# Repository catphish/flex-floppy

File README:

NOTE: This project was never completed and will receive no further updates.

Please consider greaseweazle instead: https://github.com/keirf/greaseweazle

This repository remains only for reference.

========== FlexFloppy ===========
USB Multi-pupose Floppy Interface
=================================

This device allows floppy disks to be read and written using a low cost
USB interface and a generic floppy disk drive. It is targetted at
Amiga floppy disks but may support others. Currently only DD disks
are supported due to USB FS bandwidth constraints.

Data is read and written in raw flux format and will be stored in SCP
format for for maximum compatibility and flexibility.

This project is a work in progress.

Firmware TODO
=============
Timeout on missing index pulse during write

Host TODO
=========
Proper CLI toolkit
GUI

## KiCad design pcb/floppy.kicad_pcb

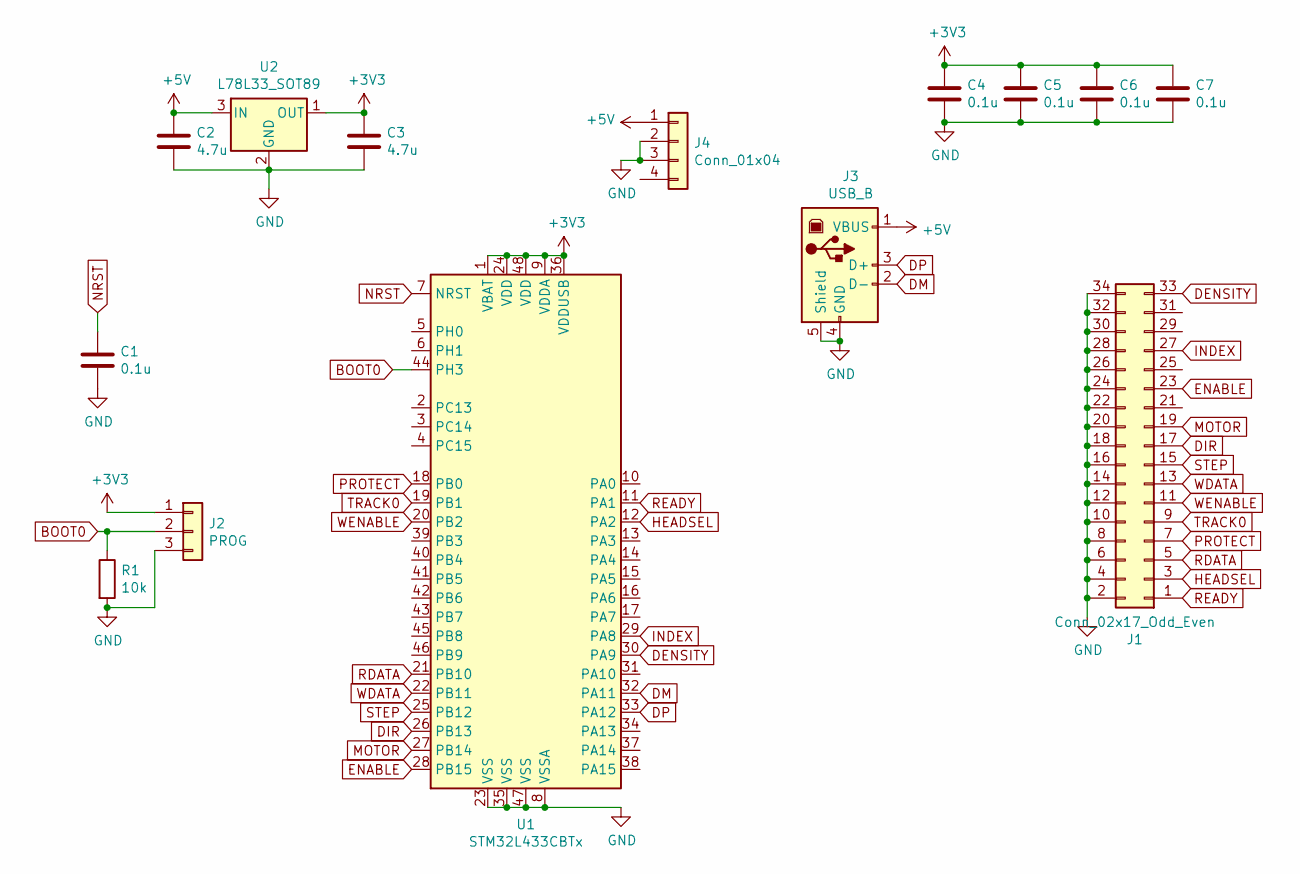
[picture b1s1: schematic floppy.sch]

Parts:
C1, C4, C5, C6, C7: 0.1u; C_0603_1608Metric
C2, C3: 4.7u; C_0603_1608Metric
J1: Conn_02x17_Odd_Even; PinSocket_2x17_P2.54mm_Horizontal
J2: PROG; PinHeader_1x03_P2.54mm_Vertical
J3: USB_B; USB_B_OST_USB-B1HSxx_Horizontal
J4: Conn_01x04; PinHeader_1x04_P2.54mm_Vertical
R1: 10k; R_0603_1608Metric
U1: STM32L433CBTx; LQFP-48_7x7mm_P0.5mm
U2: L78L33_SOT89; SOT-89-3

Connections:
+3V3: C3.1, C4.1, C5.1, C6.1, C7.1, J2.1, U1.1 (VBAT), U1.9 (VDDA), U1.24 (VDD), U1.36 (VDDUSB), U1.48 (VDD), U2.1 (OUT)
+5V: C2.1, J3.1 (VBUS), J4.1, U2.3 (IN)
BOOT0: J2.2, R1.1, U1.44 (PH3)
DENSITY: J1.33, U1.30 (PA9)
DIR: J1.17, U1.26 (PB13)
DM: J3.2 (D-), U1.32 (PA11)
DP: J3.3 (D+), U1.33 (PA12)
ENABLE: J1.23, U1.28 (PB15)
GND: C1.2, C2.2, C3.2, C4.2, C5.2, C6.2, C7.2, J1.2, J1.4, J1.6, J1.8, J1.10, J1.12, J1.14, J1.16, J1.18, J1.20, J1.22, J1.24, J1.26, J1.28, J1.30, J1.32, J1.34, J2.3, J3.4 (GND), J3.5 (Shield), J4.2, J4.3, R1.2, U1.8 (VSSA), U1.23 (VSS), U1.35 (VSS), U1.47 (VSS), U2.2 (GND)
HEADSEL: J1.3, U1.12 (PA2)
INDEX: J1.27, U1.29 (PA8)
MOTOR: J1.19, U1.27 (PB14)
NRST: C1.1, U1.7 (NRST)
PROTECT: J1.7, U1.18 (PB0)
RDATA: J1.5, U1.21 (PB10)
READY: J1.1, U1.11 (PA1)
STEP: J1.15, U1.25 (PB12)
TRACK0: J1.9, U1.19 (PB1)
WDATA: J1.13, U1.22 (PB11)
WENABLE: J1.11, U1.20 (PB2)

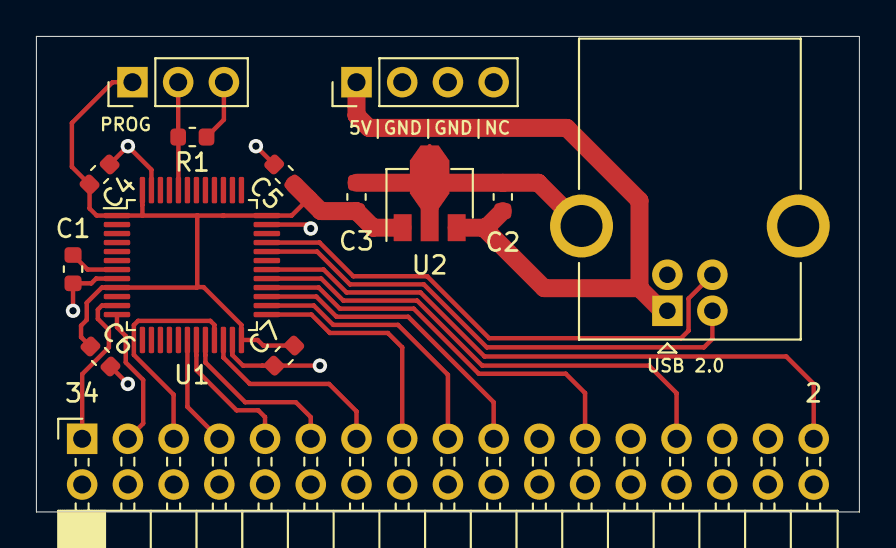
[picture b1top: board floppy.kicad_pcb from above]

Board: 2 copper layers, 45.7 x 26.4 mm, 14 parts (0 on the bottom side), 20 nets.

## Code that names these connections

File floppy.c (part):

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
  gpio_port_mode(GPIOA, 1, 0, 0, 1, 0);  // A1  READY     IN
  gpio_port_mode(GPIOA, 2, 1, 0, 0, 1);  // A2  HEADSELET OUT
  gpio_port_mode(GPIOA, 8, 0, 0, 1, 0);  // A8  INDEX     IN
  gpio_port_mode(GPIOA, 9, 1, 0, 0, 1);  // A9  DENSITY   OUT

  gpio_port_mode(GPIOB, 0, 0, 0, 1, 0);  // B0  PROTECT   IN
  gpio_port_mode(GPIOB, 1, 0, 0, 1, 0);  // B1  TRACK0    IN
  gpio_port_mode(GPIOB, 2, 1, 0, 0, 1);  // B2  WENABLE   OUT

  gpio_port_mode(GPIOB, 10, 2, 1, 1, 0); // B10 RDATA     TIMER IN
  gpio_port_mode(GPIOB, 11, 2, 1, 0, 1); // B11 WDATA     TIMER OUT

  gpio_port_mode(GPIOB, 12, 1, 0, 0, 1); // B12 STEP      OUT
  gpio_port_mode(GPIOB, 13, 1, 0, 0, 1); // B13 DIR       OUT

  gpio_port_mode(GPIOB, 14, 1, 0, 0, 1); // B14 MOTOR     OUT
  gpio_port_mode(GPIOB, 15, 1, 0, 0, 1); // B15 ENABLE    OUT

  cached_track = -1;
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
void floppy_enable() {
  GPIOB->BSRR = (1<<(16+15)); // Enable
  GPIOB->BSRR = (1<<(16+14)); // Motor on
  floppy_enabled = 1;
}
void floppy_disable() {
  GPIOB->BSRR = (1<<(14)); // Motor off
  GPIOB->BSRR = (1<<(15)); // Disable
  floppy_enabled = 0;
}
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
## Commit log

2019-05-05 Initial commit with README
2019-05-06 initial commit, mostly test code
2019-08-25 start working with l433
2019-08-27 starters of USB driver
2019-08-29 get usb working :)
2019-08-29 remove unused debug lines
2019-08-29 move descriptors to header file
2019-09-02 lots more on usb
2019-09-03 remove uart, new gpio init code, begin re-adding floppy code
2019-09-04 working streaming of flux data to usb
2019-09-09 use interrupt routine to handle timer data, add msleep, fix data buffer offset bug
2019-09-22 unknwon improvements
2019-09-29 switch to hardware ADF deode
2019-09-29 add CLI read test cool
2019-09-29 add pcb
2019-09-29 remove old readme
2019-10-01 intelligent reads with checksum checking
2019-10-02 begin experimental mass storage endpoints
2019-10-02 add MIT licence
2019-10-06 incomplete work on mass storage
2019-10-07 small demo of double buffered usb endpoint, doesn't improve performance to a worthwhile extent
2019-10-07 revert to raw flux, optimize usb
2019-10-08 more minor flux read optimizaions, create host side flux storage format and begin adf decoder
2019-10-08 transmit delta timings over usb protocol, finish basic adf decoder
2019-10-11 new variable length encoding
2019-10-14 higher performance libusb reads
2019-10-14 begin write code
2019-10-15 working writes
2019-10-19 major rewrite to move all operations (except timer interrupts) into a single event loop
2019-10-19 reimplement writes
2019-10-22 stability fixes
2019-10-23 major rework so better scope functions and improve performance (read-only)
2019-10-23 reimplement writes in new framework
2019-10-23 minor fixes
2019-10-23 change resolution to 40MHz, minor stability fixes
2019-10-24 add index pulse information, always use separate usb transfer for status, add read retries
2019-10-24 add documentation
2019-10-26 fix pulse time, remove legacy adf decoder, add read and write scp support
2019-10-28 add USB software update jumper
2019-10-29 USB double buffering
2019-10-31 use dummy packet size to mark unused rx buffers
2019-10-31 start reading and writing at index pulse
2019-11-01 reduce large capacitors
2019-11-04 usb documentation
2019-11-05 don't perform read actions when index pulses occur during write. terminate write on index pulse
2019-11-07 begin cross-platform wxwidgets / libusb gui
2019-11-13 begin usb reads in GUI
2019-11-14 grid status display
2019-11-25 basic mass storage implementation (no drive access yet)
2019-11-26 fully working read-only access
2019-11-30 faster stepping, power off motor when not in use
2019-12-01 write support
2019-12-03 mass storage improvements for windows support
2026-01-22 Update README with project completion note
    Added a note indicating project status and reference.
2026-01-22 Revise project note and recommend greaseweazle
    Updated project status and recommendation for greaseweazle.
